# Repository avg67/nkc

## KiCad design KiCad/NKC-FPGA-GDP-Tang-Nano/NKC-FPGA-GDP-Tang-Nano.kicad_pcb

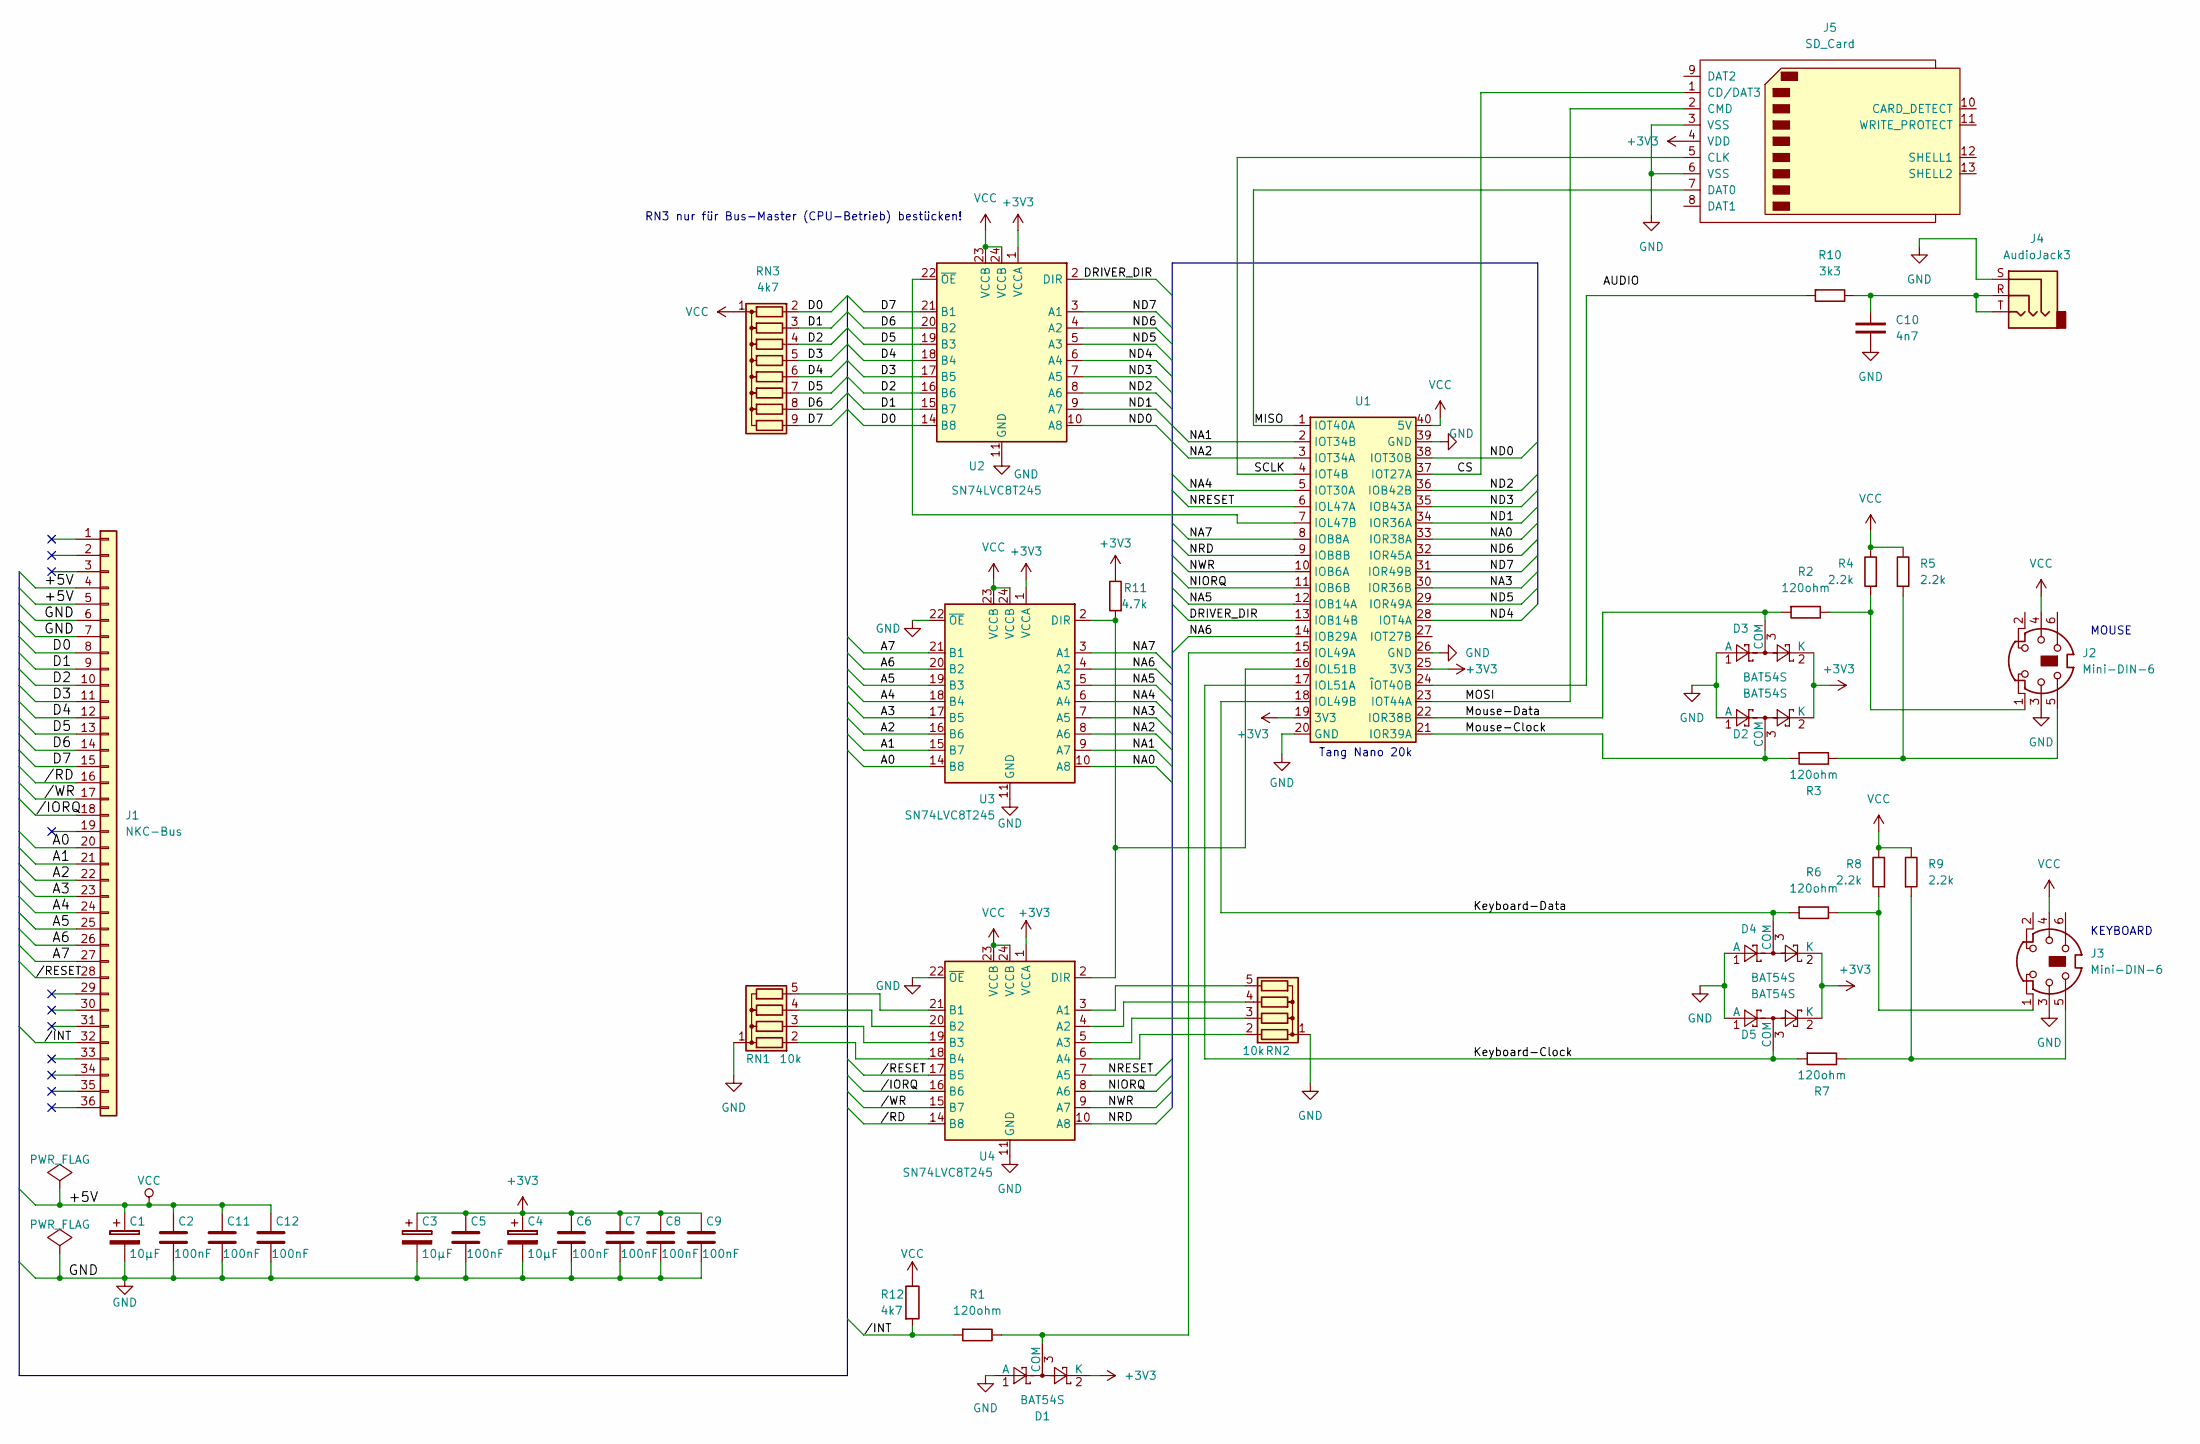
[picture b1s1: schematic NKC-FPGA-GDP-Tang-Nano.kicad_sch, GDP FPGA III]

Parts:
C1, C3, C4: 10µF; CP_EIA-3528-21_Kemet-B
C2, C5, C6, C7, C8, C9, C11, C12: 100nF; C_1206_3216Metric
C10: 4n7; C_1206_3216Metric
D1, D2, D3, D4, D5: BAT54S; SOT-23
J1: NKC-Bus; PinHeader_1x36_P2.54mm_Horizontal
J2, J3: Mini-DIN-6; Connector_Mini-DIN_Female_6Pin_2rows
J4: AudioJack3; Jack_3.5mm_Ledino_KB3SPRS_Horizontal
J5: SD_Card; SD_Hirose_DM1AA_SF_PEJ82
R1, R2, R3, R6, R7: 120ohm; R_1206_3216Metric
R4, R5, R8, R9: 2.2k; R_1206_3216Metric
R10: 3k3; R_1206_3216Metric
R11: 4.7k; R_1206_3216Metric
R12: 4k7; R_1206_3216Metric
RN1, RN2: 10k; R_Array_SIP5
RN3: 4k7; R_Array_SIP9
U1: DIP-40_W20.3mm_Socket
U2, U3, U4: SN74LVC8T245; SOIC-24W_7.5x15.4mm_P1.27mm

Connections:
+3V3: C3.1, C4.1, C5.1, C6.1, C7.1, C8.1, C9.1, D1.2 (K), D2.2 (K), D3.2 (K), D4.2 (K), D5.2 (K), J5.4 (VDD), R11.2, U1.19 (3V3), U1.25 (3V3), U2.1 (VCCA), U3.1 (VCCA), U4.1 (VCCA)
/A0: J1.20, U3.14 (B8)
/A1: J1.21, U3.15 (B7)
/A2: J1.22, U3.16 (B6)
/A3: J1.23, U3.17 (B5)
/A4: J1.24, U3.18 (B4)
/A5: J1.25, U3.19 (B3)
/A6: J1.26, U3.20 (B2)
/A7: J1.27, U3.21 (B1)
/CS: J5.1 (CD/DAT3), U1.37 (IOT27A)
/D0: J1.8, RN3.2 (R1), U2.14 (B8)
/D1: J1.9, RN3.3 (R2), U2.15 (B7)
/D2: J1.10, RN3.4 (R3), U2.16 (B6)
/D3: J1.11, RN3.5 (R4), U2.17 (B5)
/D4: J1.12, RN3.6 (R5), U2.18 (B4)
/D5: J1.13, RN3.7 (R6), U2.19 (B3)
/D6: J1.14, RN3.8 (R7), U2.20 (B2)
/D7: J1.15, RN3.9 (R8), U2.21 (B1)
/DRIVER_DIR: U1.13 (IOB14B), U2.2 (DIR)
/Keyboard-Clock: D5.3 (COM), R7.1, U1.17 (IOL51A)
/Keyboard-Data: D4.3 (COM), R6.1, U1.18 (IOL49B)
/MISO: J5.7 (DAT0), U1.1 (IOT40A)
/MOSI: J5.2 (CMD), U1.23 (IOT44A)
/Mouse-Clock: D2.3 (COM), R3.1, U1.21 (IOR39A)
/Mouse-Data: D3.3 (COM), R2.1, U1.22 (IOR38B)
/NA0: U1.33 (IOR38A), U3.10 (A8)
/NA1: U1.2 (IOT34B), U3.9 (A7)
/NA2: U1.3 (IOT34A), U3.8 (A6)
/NA3: U1.30 (IOR36B), U3.7 (A5)
/NA4: U1.5 (IOT30A), U3.6 (A4)
/NA5: U1.12 (IOB14A), U3.5 (A3)
/NA6: U1.14 (IOB29A), U3.4 (A2)
/NA7: U1.8 (IOB8A), U3.3 (A1)
/ND0: U1.38 (IOT30B), U2.10 (A8)
/ND1: U1.34 (IOR36A), U2.9 (A7)
/ND2: U1.36 (IOB42B), U2.8 (A6)
/ND3: U1.35 (IOB43A), U2.7 (A5)
/ND4: U1.28 (IOT4A), U2.6 (A4)
/ND5: U1.29 (IOR49A), U2.5 (A3)
/ND6: U1.32 (IOR45A), U2.4 (A2)
/ND7: U1.31 (IOR49B), U2.3 (A1)
/NIORQ: U1.11 (IOB6B), U4.8 (A6)
/NRD: U1.9 (IOB8B), U4.10 (A8)
/NRESET: U1.6 (IOL47A), U4.7 (A5)
/NWR: U1.10 (IOB6A), U4.9 (A7)
/SCLK: J5.5 (CLK), U1.4 (IOT4B)
//INT: J1.32, R1.1, R12.2
//RESET: J1.28, U4.17 (B5)
GND: C1.2, C2.2, C3.2, C4.2, C5.2, C6.2, C7.2, C8.2, C9.2, C10.2, C11.2, C12.2, D1.1 (A), D2.1 (A), D3.1 (A), D4.1 (A), D5.1 (A), J1.6, J1.7, J2.3, J3.3, J4.S, J5.3 (VSS), J5.6 (VSS), RN1.1 (common), RN2.1 (common), U1.20 (GND), U1.26 (GND), U1.39 (GND), U2.11 (GND), U2.12 (GND), U2.13 (GND), U3.11 (GND), U3.12 (GND), U3.13 (GND), U3.22 (~OE), U4.11 (GND), U4.12 (GND), U4.13 (GND), U4.22 (~OE)
unnamed: C10.1, J4.R, J4.T, R10.2
unnamed: D1.3 (COM), R1.2, U1.15 (IOL49A)
unnamed: J2.1, R2.2, R4.1
unnamed: J2.5, R3.2, R5.1
unnamed: J3.1, R6.2, R8.1
unnamed: J3.5, R7.2, R9.1
unnamed: RN1.2 (R1), U4.18 (B4)
unnamed: RN1.3 (R2), U4.19 (B3)
unnamed: RN1.4 (R3), U4.20 (B2)
unnamed: RN1.5 (R4), U4.21 (B1)
unnamed: RN2.2 (R1), U4.6 (A4)
unnamed: RN2.3 (R2), U4.5 (A3)
unnamed: RN2.4 (R3), U4.4 (A2)
unnamed: RN2.5 (R4), U4.3 (A1)
unnamed: U1.7 (IOL47B), U2.22 (~OE)
unnamed: R11.1, U1.16 (IOL51B), U3.2 (DIR), U4.2 (DIR)
unnamed: R10.1, U1.24 (ÎOT40B)
VCC: C1.1, C2.1, C11.1, C12.1, J1.4, J1.5, J2.4, J3.4, R4.2, R5.2, R8.2, R9.2, R12.1, RN3.1 (common), U1.40 (5V), U2.23 (VCCB), U2.24 (VCCB), U3.23 (VCCB), U3.24 (VCCB), U4.23 (VCCB), U4.24 (VCCB)

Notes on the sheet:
KEYBOARD
Tang Nano 20k
MOUSE
RN3 nur für Bus-Master (CPU-Betrieb) bestücken!

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
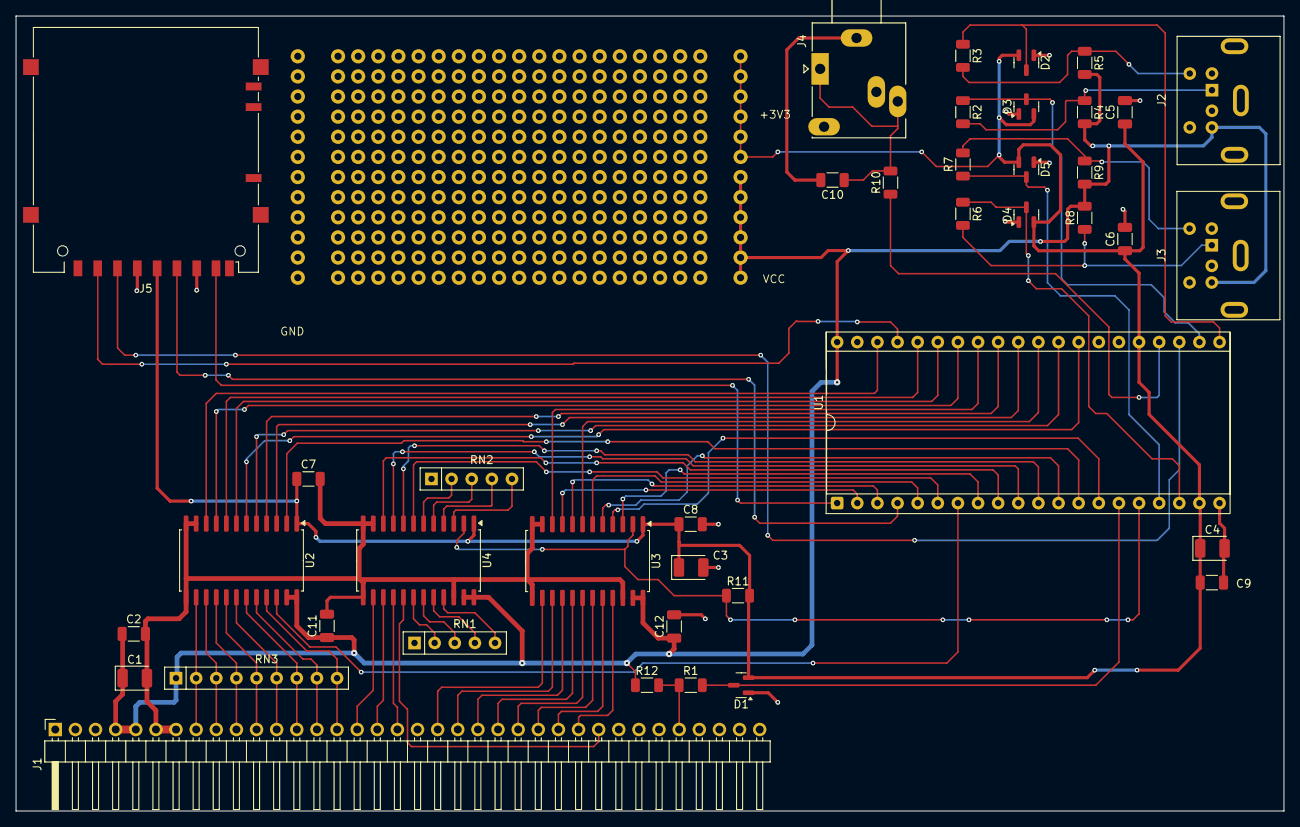
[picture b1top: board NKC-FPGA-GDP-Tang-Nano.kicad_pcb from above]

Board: 2 copper layers, 160.0 x 100.3 mm, 41 parts (0 on the bottom side), 70 nets.

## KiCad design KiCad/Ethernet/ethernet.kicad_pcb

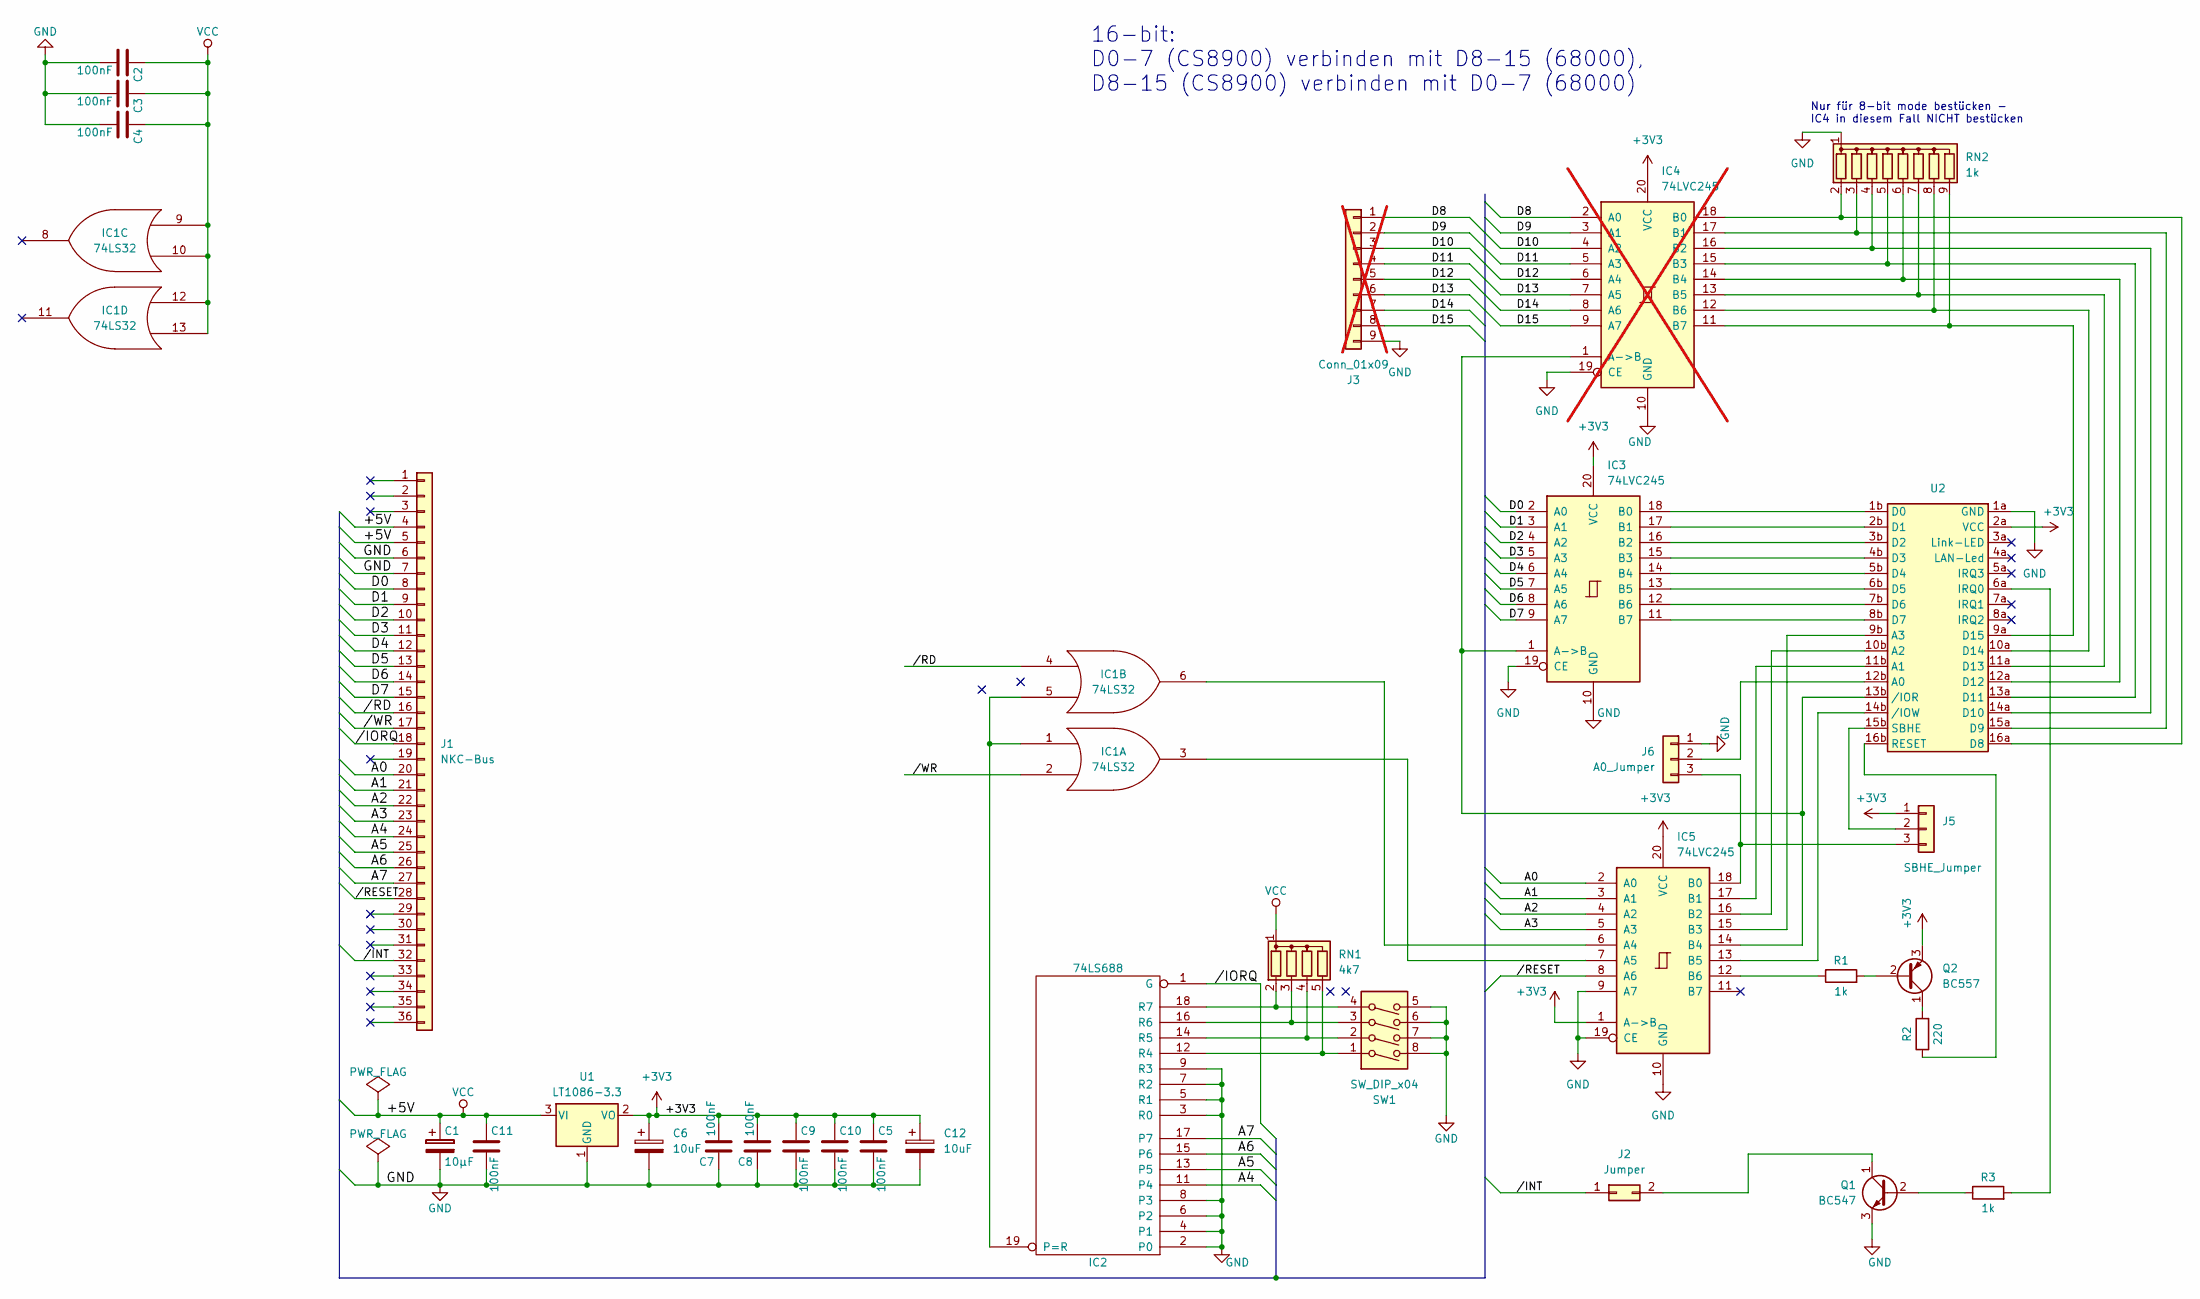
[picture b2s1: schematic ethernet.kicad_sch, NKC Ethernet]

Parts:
C1: 10µF; CP_Radial_D5.0mm_P2.50mm
C2, C3, C4, C5, C7, C8, C9, C10, C11: 100nF; C_Disc_D5.0mm_W2.5mm_P5.00mm
C6, C12: 10uF; CP_Radial_D5.0mm_P2.50mm
IC1: 74LS32; DIP-14_W7.62mm_LongPads
IC2: 74LS688; DIP-20_W7.62mm_LongPads
IC3, IC5: 74LVC245; DIP-20_W7.62mm_LongPads
IC4: 74LVC245; DIP-20_W7.62mm_LongPads; not fitted
J1: NKC-Bus; PinHeader_1x36_P2.54mm_Horizontal
J2: Jumper; PinHeader_1x02_P2.54mm_Vertical
J3: Conn_01x09; PinHeader_1x09_P2.54mm_Vertical; not fitted
J5: SBHE_Jumper; PinHeader_1x03_P2.54mm_Vertical
J6: A0_Jumper; PinHeader_1x03_P2.54mm_Vertical
Q1: BC547; TO-92_Inline_Wide
Q2: BC557; TO-92_Inline_Wide
R1, R3: 1k; R_Axial_DIN0207_L6.3mm_D2.5mm_P10.16mm_Horizontal
R2: 220; R_Axial_DIN0207_L6.3mm_D2.5mm_P10.16mm_Horizontal
RN1: 4k7; R_Array_SIP5
RN2: 1k; R_Array_SIP9
SW1: SW_DIP_x04; SW_DIP_SPSTx04_Slide_6.7x11.72mm_W7.62mm_P2.54mm_LowProfile
U1: LT1086-3.3; TO-220-3_Horizontal_TabDown
U2: Olimex CS8900A-H

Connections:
+3V3: C5.1, C6.1, C7.2, C8.2, C9.1, C10.1, C12.1, IC3.20 (VCC), IC4.20 (VCC), IC5.1 (A->B), IC5.20 (VCC), J5.1, Q2.3 (E), U1.2 (VO), U2.2a (VCC)
/A0: IC5.2 (A0), J1.20
/A1: IC5.3 (A1), J1.21
/A2: IC5.4 (A2), J1.22
/A3: IC5.5 (A3), J1.23
/A4: IC2.11 (P4), J1.24
/A5: IC2.13 (P5), J1.25
/A6: IC2.15 (P6), J1.26
/A7: IC2.17 (P7), J1.27
/D0: IC3.2 (A0), J1.8
/D1: IC3.3 (A1), J1.9
/D2: IC3.4 (A2), J1.10
/D3: IC3.5 (A3), J1.11
/D4: IC3.6 (A4), J1.12
/D5: IC3.7 (A5), J1.13
/D6: IC3.8 (A6), J1.14
/D7: IC3.9 (A7), J1.15
/D8: IC4.2 (A0), J3.1
/D9: IC4.3 (A1), J3.2
/D10: IC4.4 (A2), J3.3
/D11: IC4.5 (A3), J3.4
/D12: IC4.6 (A4), J3.5
/D13: IC4.7 (A5), J3.6
/D14: IC4.8 (A6), J3.7
/D15: IC4.9 (A7), J3.8
//INT: J1.32, J2.1
//IORQ: IC2.1 (G), J1.18
//RESET: IC5.8 (A6), J1.28
GND: C1.2, C2.2, C3.2, C4.2, C5.2, C6.2, C7.1, C8.1, C9.2, C10.2, C11.2, C12.2, IC1.7 (GND), IC2.2 (P0), IC2.3 (R0), IC2.4 (P1), IC2.5 (R1), IC2.6 (P2), IC2.7 (R2), IC2.8 (P3), IC2.9 (R3), IC2.10 (GND), IC3.10 (GND), IC3.19 (CE), IC4.10 (GND), IC4.19 (CE), IC5.9 (A7), IC5.10 (GND), IC5.19 (CE), J1.6, J1.7, J3.9, J6.1, Q1.3 (E), RN2.1 (common), SW1.5, SW1.6, SW1.7, SW1.8, U1.1 (GND), U2.1a (GND)
unnamed: IC1.1, IC1.5, IC2.19 (P=R)
unnamed: IC2.12 (R4), RN1.5 (R4), SW1.1
unnamed: IC2.14 (R5), RN1.4 (R3), SW1.2
unnamed: IC2.16 (R6), RN1.3 (R2), SW1.3
unnamed: IC2.18 (R7), RN1.2 (R1), SW1.4
unnamed: IC3.1 (A->B), IC4.1 (A->B), IC5.14 (B4), U2.13b (/IOR)
unnamed: IC3.18 (B0), U2.1b (D0)
unnamed: IC3.17 (B1), U2.2b (D1)
unnamed: IC3.16 (B2), U2.3b (D2)
unnamed: IC3.15 (B3), U2.4b (D3)
unnamed: IC3.14 (B4), U2.5b (D4)
unnamed: IC3.13 (B5), U2.6b (D5)
unnamed: IC3.12 (B6), U2.7b (D6)
unnamed: IC3.11 (B7), U2.8b (D7)
unnamed: IC4.18 (B0), RN2.2 (R1), U2.16a (D8)
unnamed: IC4.17 (B1), RN2.3 (R2), U2.15a (D9)
unnamed: IC4.16 (B2), RN2.4 (R3), U2.14a (D10)
unnamed: IC4.15 (B3), RN2.5 (R4), U2.13a (D11)
unnamed: IC4.14 (B4), RN2.6 (R5), U2.12a (D12)
unnamed: IC4.13 (B5), RN2.7 (R6), U2.11a (D13)
unnamed: IC4.12 (B6), RN2.8 (R7), U2.10a (D14)
unnamed: IC4.11 (B7), RN2.9 (R8), U2.9a (D15)
unnamed: IC1.6, IC5.6 (A4)
unnamed: IC1.3, IC5.7 (A5)
unnamed: IC5.18 (B0), J5.3, J6.3
unnamed: IC5.17 (B1), U2.11b (A1)
unnamed: IC5.16 (B2), U2.10b (A2)
unnamed: IC5.15 (B3), U2.9b (A3)
unnamed: IC5.13 (B5), U2.14b (/IOW)
unnamed: IC5.12 (B6), R1.1
unnamed: J2.2, Q1.1 (C)
unnamed: J5.2, U2.15b (SBHE)
unnamed: J6.2, U2.12b (A0)
unnamed: Q1.2 (B), R3.1
unnamed: Q2.2 (B), R1.2
unnamed: Q2.1 (C), R2.2
unnamed: R3.2, U2.6a (IRQ0)
unnamed: R2.1, U2.16b (RESET)
VCC: C1.1, C2.1, C3.1, C4.1, C11.1, IC1.9, IC1.10, IC1.12, IC1.13, IC1.14 (VCC), IC2.20 (VCC), J1.4, J1.5, RN1.1 (common), U1.3 (VI)

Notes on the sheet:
Nur für 8-bit mode bestücken - IC4 in diesem Fall NICHT bestücken
16-bit: D0-7 (CS8900) verbinden mit D8-15 (68000), D8-15 (CS8900) verbinden mit D0-7 (68000)

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
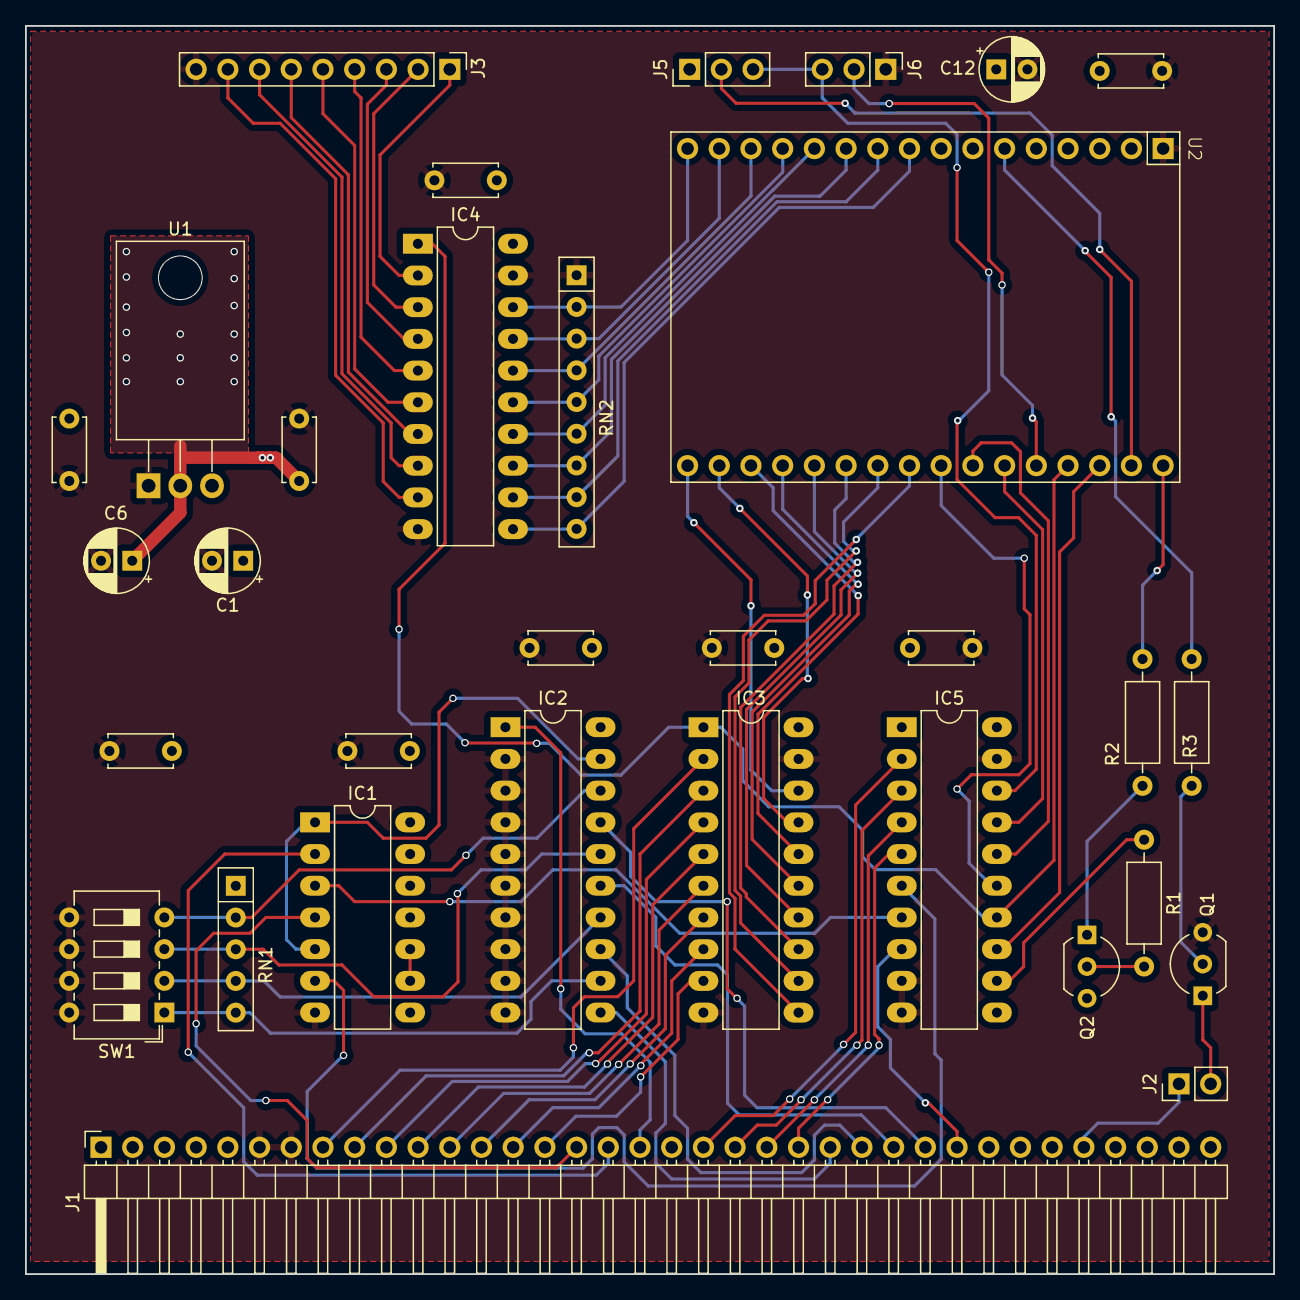
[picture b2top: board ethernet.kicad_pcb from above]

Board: 2 copper layers, 100.0 x 100.0 mm, 32 parts (0 on the bottom side), 70 nets.

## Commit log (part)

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2021-06-12 initial version
2021-06-13 update - added macro for SER overflow check
2021-12-12 initial checkin
2021-12-30 added 512x512x256color video mode
2022-01-01 updates & bugfixes
2022-01-30 update spi, bugfix for Video
2022-07-01 added gdp_en signal
2022-08-27 update. 4bit color mode now working properly. 8bit still buggy
2022-09-08 final update for video
2022-09-30 Jados Example initial version
2022-09-30 new file
2022-10-02 update change dir to 4 columns
2022-10-05 update - save and display highscore now
2022-10-10 Bugfix for Highscore list and Stone rotation
2022-10-29 added Sound
2023-01-02 delta against SysGCC download for NKC
2023-01-06 bugfix
2023-01-11 update for C++
2023-01-17 update to new version with 3D effects
2023-02-02 added interrupts for Ser1
2023-02-05 updates for C++
2023-02-05 bugfix for highscore list
2023-02-05 Monochrome version of Minesweeper which should run on original GDP
2023-02-08 bugfix for ser-irq
2023-02-08 update ser1
2023-02-26 TFTP Bootloader using CS8900 Ethernet Controller - initial Version
2023-02-26 update for DHCP
2023-03-04 update - added dry-run option
2023-05-30 Initial Version of 68k System for HPE_MINI_LEC - Flash programmer
2023-05-30 update header
2023-10-22 Added keyboard mode
2023-10-29 Update - added highscore
2023-10-30 Some updates
2023-11-05 added Initial version of Bootloader with CS8900 Ethernet Controller
2023-11-05 Python tftp client
2023-11-06 update TFTP-BL
2023-11-09 update makefile
2023-11-22 initial version of Ethernet Schematic
2023-11-23 initial version of Minesweeper using dynamic memory allocation
2023-12-08 Added layout
2023-12-12 update makefile for multiple threads
2024-01-31 added schematic for GDP-FPGA V1
2024-02-19 Added Jados Bootdisk containing minesweeper and Spaceinvaders
2024-08-05 initial version for Tang-Nano 20k
2024-09-13 Added PCB-fix
2024-09-21 update GDP-FPGA for Tang-nano
2024-09-21 minor bugfix
2024-09-21 Programmer file for Tang nano 20k
2024-09-27 remap some pins to enable SDCARD usage
2024-09-27 Cleanup
2024-09-28 update pin assignement
2024-09-28 update FPGA pin assignement, added PS/2 interfaces
2024-10-06 update added sound, ps2kbd, Mouse, Ser, SD-Card, Timer
2024-10-13 update 256 color mode palette rg. to ANSI
2024-10-19 disabled everything except timer.
2024-11-04 update - better center picture
2024-11-06 added FPGA file with GDP, Timer and SD-Card (SPI)
2024-11-06 update - center screen on HDMI
2024-11-07 color demo added
2024-11-07 Color Mandelbrot added
2024-11-09 Initial Version of NKC (with 10MHz 68000 CPU) and GP7.10r5
2024-11-10 NKC for Tang Nano 20k with KEY from USB via Terminal 9600 Baud
2024-11-16 Jados SDCard Image (1GB) for Tang nano 20k
2024-11-17 Initial Version of NKC68K16
2024-11-24 NKC inklusive PS2-Key and ext. Businterface
2024-12-09 Added 2ns SD-Card
2024-12-09 New FPGA File with 2nd SD-Card and Patched GP7.10R6 for better compatiblity with SD-Cards
2024-12-10 added README.md
2024-12-10 updste
2024-12-19 optimized SDRAM-access. Resulting speed-up ~20%
2024-12-21 update SDRAM-Controller for NKC-SOC
2025-01-05 update for external Interrupts
2025-01-23 uUpdate NKC_ser_key, Added Z80 with ser. Key
2025-01-26 update disk image
2025-01-27 update - Z80 added
2025-01-31 update Level shifter to 74LVC8T245
2025-02-20 Initial Version of SysGCC Framework for NKC
2025-02-27 update & cleanup
2025-02-27 added .s19 file to standard outputs
2025-03-13 added FPGA file for UWE's PCB
2025-04-10 added missing files, changed path to relative
2025-04-10 rename
2025-05-06 Speed optimization - set sdram-clock to 80MHz
2025-05-09 update Z80
2025-05-20 added documentation for GDP-FPGA
2025-05-20 added port description
2025-05-22 added infos about FPGA Programming
2025-05-24 added Foto of GDP-FPGA
2025-07-03 some updates - SD-Card speed optimizations for GP routines
2025-07-03 update - SD-card speed optimizations for GP routines
2025-07-06 Added patched GP 7.10r6 (SD-Card routines speedup)
2025-07-15 update, add missing files
2025-07-19 added GDP64HS-FPGA file für PCB von Uwe
2025-07-21 update to latest version
2025-07-22 updates, bugfixes for PCB
2025-07-28 added new Z80 FPGA image with ALL Roms
2025-08-01 added FPGA file for Tang-Nano only with GDP64-HS
2025-08-01 added disable switch for GDP, cleanup
2025-08-01 Added missing files
2025-08-05 bugfix for monochrome mode, added SDIO for Z80 support
2025-08-06 move old FPGA files into archive
2025-08-06 rename folder
2025-08-06 Added FPGA file with new (4-5 times faster) CPU
2025-08-10 update Gowin 68k-SOC workspace
2025-08-10 update Gowin Workspace for Z80-SOC
2025-08-11 update for S/W mode
2025-08-12 added Reset via CTRX-ALT-DELETE or CTRX-ESC
2025-08-14 update Z80 Gowin Settings
2025-08-14 rename 68k-SOC Workspace
2025-08-14 renamed Z80-Soc
2025-09-08 Initial Version of Sound-demo
2025-09-17 Added updated Kicad file
2025-10-07 update GP to 7.11 to fix SD-Card issues
2025-10-08 add GP710r7
2025-10-08 New fpga file to fix small issue in GP
2025-10-08 update GP binary
2025-11-12 added binary file for 68008
2025-11-15 Added Gotek Disk Image
2025-11-25 fix sound problems with HDMI for GDP-FPGA
2025-11-25 new fpgafile for GDP-FPGA to fix sound problems with HDMI
2025-11-28 bugfix for HDMI-Sound output
2025-11-28 Bugfix for HDMI Sound output
2025-11-28 update connection of dac to unsigned signal
2025-12-05 Update newlib_stubs.c to fix Cursor problems
    Missing blinking cursor in terminal when getcon is called
2025-12-17 bugfixes for some inline function for uint8_t datatypes
2025-12-22 bugfix for ext. businterface - FLO2 now working!
2025-12-23 remove obsolete file
2025-12-23 added source of fast 68k SOC
2025-12-23 update missing file
2025-12-23 update missing files
2026-01-01 update ctr0.s for -O0
2026-01-04 update linker-script to add libm
2026-01-05 bugfix for crt0.c
2026-01-05 update mouse - improved resolution and speed
2026-01-20 added CLUT XLS
2026-01-27 Update CLUT to 24bit, enabled CLUT-read
2026-01-27 update CLUT register definitions
2026-01-31 re-create FPGA file for fast CPU, added GP Source for fast CPU
2026-01-31 update for 24bit CLUT
2026-02-05 Added FPGA-file with 68k SOC which supports (most) 68020 Instructions
2026-03-05 added I2C Master routines
2026-03-08 added I2C Datasheet for Tang-Nano
2026-03-08 Added I2C
2026-03-12 added library for HW-I2C
2026-03-16 update regular 68k SOC FPGA file with I2C, apply patches for better SD-Card compatility to GP for 68020
2026-03-19 added I2C to Z80 SOC
2026-03-19 added Z80 FPGA file with I2C
2026-03-26 Added Memory init after power-up, added Reset-info Register
2026-03-28 added FPGA file with EDID support and SW-Application to read and display it
2026-03-28 added I2C Library for Turbo-Pascal 2.X
2026-03-31 update fast 68000 CPU with I2C and EDID Interface
2026-04-14 update ser-key
2026-04-19 update - add tao file for CPU
2026-04-21 added missing Z80 FPGA file
2026-05-04 Added Schematic for NKC_SOC with Ethernet Phy
2026-06-16 added new FPGA files with Cache
